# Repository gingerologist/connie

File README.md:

# Connie

Constance Emily Kent, the murder at Road Hill House.

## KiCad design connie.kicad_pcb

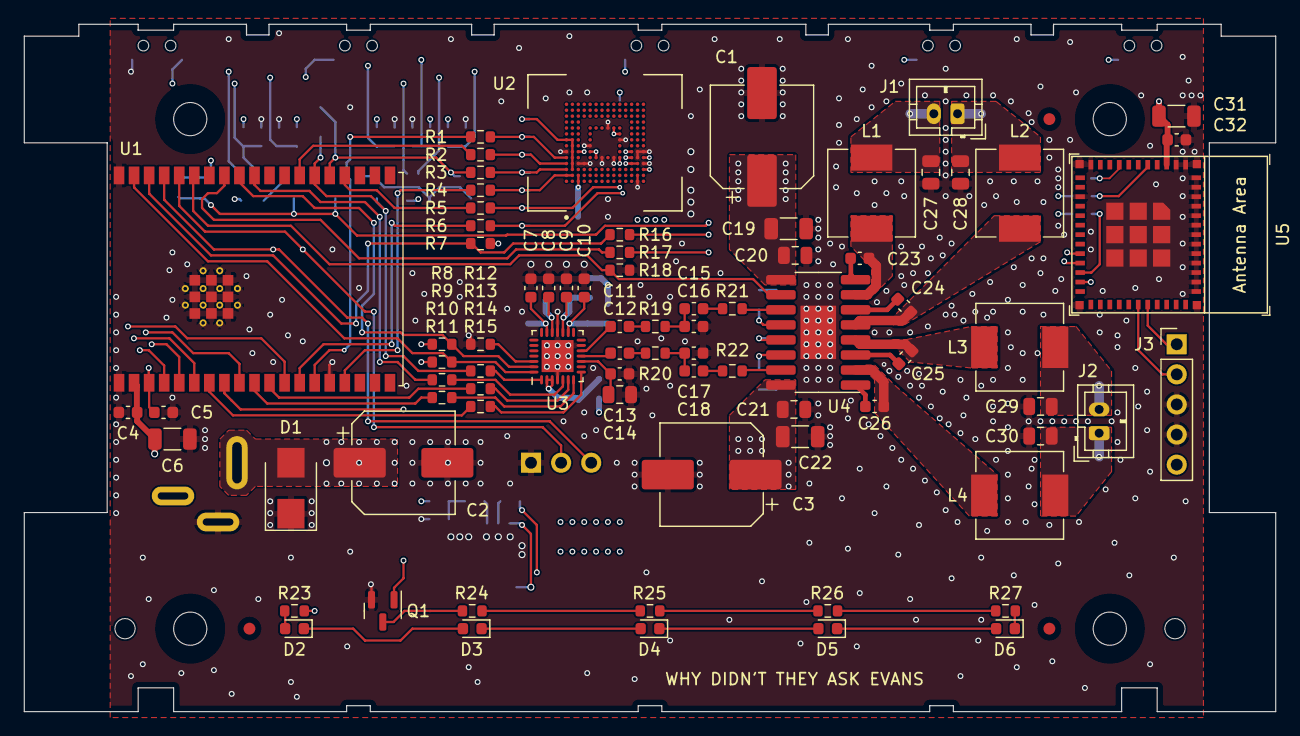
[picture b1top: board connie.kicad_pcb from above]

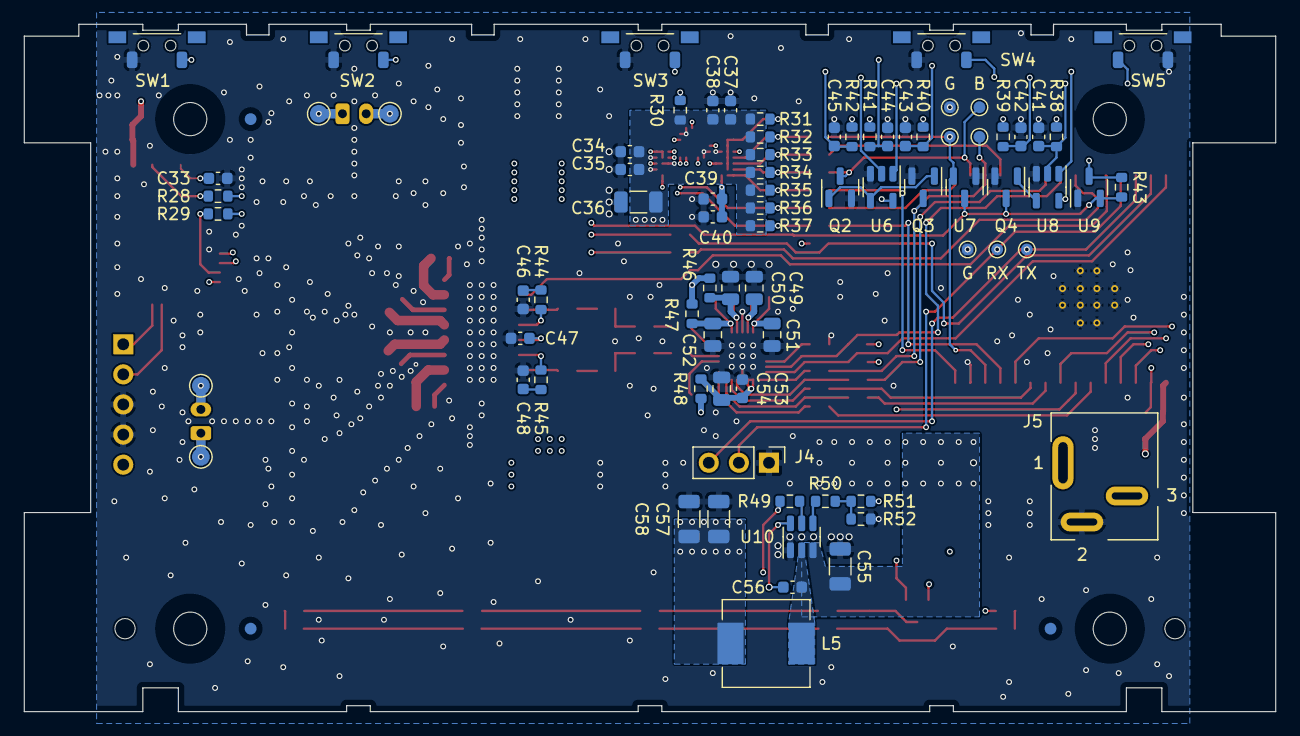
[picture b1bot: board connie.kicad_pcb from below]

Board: 4 copper layers, 105.6 x 58.0 mm, 168 parts (81 on the bottom side), 100 nets.

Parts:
C1, C2, C3: 220u,35V; CP_Elec_8x10.5
C4, C5, C7, C8, C9, C10, C13, C32, C33, C34, C37, C39, C41, C42, C43, C44, C45, C53: 0.1u; C_0603_1608Metric
C6, C19, C22, C31, C36, C55, C57, C58: 22u,1206,50V; C_1206_3216Metric
C11, C12, C15, C18, C35, C38, C40, C46, C48: 2.2u; C_0603_1608Metric
C14, C49, C50, C51, C52, C54: 10u,0805; C_0805_2012Metric
C16, C17: 47p; C_0603_1608Metric
C20, C21: 0.1u,0805,50V; C_0805_2012Metric
C23, C24, C25, C26, C47, C56: 1u,50V; C_0603_1608Metric
C27, C28, C29, C30: 0.47u,0805,50V; C_0805_2012Metric
D1: SMBJ15CA; D_SMB
D2, D3, D4, D5, D6: LED; LED_0603_1608Metric
FID1, FID2, FID3, FID4, FID5, FID6: Fiducial; Fiducial_1mm_Mask2mm
H1, H2, H3, H5: MountingHole; MountingHole_2.8mm_M2.5
H4, H6: MountingHole; MountingHole_1.7mm
J1, J2: Conn_01x02; JST_PH_B2B-PH-K_1x02_P2.00mm_Vertical
J3: Conn_01x05; PinHeader_1x05_P2.54mm_Vertical
J4: Conn_01x03; PinHeader_1x03_P2.54mm_Vertical
J5: Barrel_Jack_Switch; 69410X402002
L1, L2, L3, L4, L5: 10uH; Sunlord_MWSA0603_6.6x7.1_H3.0
Q1, Q2, Q3, Q4: DTC143Z; SOT-23
R1, R2, R3, R4, R5, R6, R10, R11, R12, R13, R14, R15, R16, R17: 33; R_0603_1608Metric
R7, R49: 100k; R_0603_1608Metric
R8, R9: 2.2k; R_0603_1608Metric
R18, R28, R29, R30, R31, R32, R33, R34, R35, R36, R37, R38, R39, R40, R41, R42, R43, R50: 10k; R_0603_1608Metric
R19, R20, R21, R22, R23, R24, R25, R26, R27, R44, R45: 100,1%; R_0603_1608Metric
R46, R47, R48: 0; R_0603_1608Metric
R51: 40.2k,1%; R_0603_1608Metric
R52: 13k,1%; R_0603_1608Metric
SW1, SW2, SW3, SW4, SW5: DIP_1188E
TP1, TP2, TP3, TP4, TP5, TP6, TP7: TestPoint; TestPoint_Pad_D1.0mm
TP10, TP11, TP12, TP13: TestPoint; TestPoint_Pad_D1.5mm
U1: ESP32-WROVER-E; ESP32-WROVER-E_Thermal_Vias
U2: EMMC(BGA153); EMMC_BGA153
U3: ES8388; QFN-28_EP_4x4_Pitch0.45mm
U4: CS8676E; CS8676E_SOP-16_3.9x9.9mm_P1.27mm
U5: ESP32-C3-MINI-1
U6, U8: 74LVC1G02; SOT-23-5
U7, U9: MAX803; SOT-23
U10: TPS562200; SOT-23-6

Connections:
+3V3: C4.1, C6.2, C31.2, C32.1, C34.2, C35.2, C36.2, C37.2, C38.2, C57.2, C58.2, L5.2, R7.1, R8.1, R9.1, R28.1, R29.1, R30.1, R31.1, R32.1, R33.1, R34.1, R35.1, R36.1, R37.1, R38.1, R39.2, R40.1, R41.1, R42.1, R43.1, R46.2, R47.2, R48.2, R51.1, U1.2 (3V3), U2.C6 (VCCQ), U2.E6 (VCC), U2.F5 (VCC), U2.J10 (VCC), U2.K9 (VCC), U2.M4 (VCCQ), U2.N4 (VCCQ), U2.P3 (VCCQ), U2.P5 (VCCQ), U5.3 (3V3), U6.5 (VCC), U8.5 (VCC), U9.3 (VCC)
+15V: C1.1, C2.1, C3.1, C19.2, C20.2, C21.2, C22.2, C55.2, D1.2 (A2), J5.1, R23.1, R49.2, U4.9 (PVCC), U4.16 (PVCC), U10.3 (VIN)
/C3_IO9: J3.5, U5.23 (IO9)
/C3_RXD0: J3.2, U5.30 (IO22)
/C3_RXD1: R16.2, U5.20 (IO6)
/C3_TXD0: J3.1, U5.31 (IO21)
/C3_TXD1: R17.2, U5.21 (IO7)
/CLK: R6.1, U1.13 (IO14)
/CMD: R5.1, U1.23 (IO15)
/D0: Q2.3 (C), R3.1, TP5.1, U1.24 (IO2)
/D1: R2.1, U1.26 (IO4)
/D2: R1.1, TP7.1, U1.14 (IO12), U7.2 (~RESET)
/D3: R4.1, U1.16 (IO13)
/DAT0: R3.2, R34.2, U2.A3 (DAT0)
/DAT1: R2.2, R33.2, U2.A4 (DAT1)
/DAT2: R1.2, R32.2, U2.A5 (DAT2)
/DAT3: R4.2, R35.2, U2.A2 (NC), U2.B2 (DAT3)
/DATN: R31.2, U2.A8 (NC), U2.B3 (DAT4), U2.B4 (DAT5), U2.B5 (DAT6), U2.B6 (DAT7), U2.B7 (NC), U2.B8 (NC)
/DIN: R14.1, U1.11 (IO26)
/DOUT: R15.1, U1.7 (IO35)
/EN: C5.2, C33.2, Q4.3 (C), R43.2, U1.3 (EN), U5.8 (EN), U7.3 (VCC), U9.2 (~RESET)
/LED: Q1.1 (B), U1.8 (IO32)
/LOUT1: C15.2, C16.2, R19.2
/LRCK: R11.1, U1.10 (IO25)
/MCLK: Q3.3 (C), R13.1, TP4.1, U1.25 (IO0)
/MODE: C41.2, R38.2, SW5.3, U1.5 (SENSOR_VN), U6.1, U8.2
/OUTNL: C24.1, L2.2, U4.5 (OUTNL)
/OUTNL2: C28.2, J1.1, L2.1, TP11.1
/OUTNR: C25.1, L3.2, U4.4 (OUTNR)
/OUTNR2: C29.1, J2.2, L3.1, TP13.1
/OUTPL: C23.1, L1.2, U4.7 (OUTPL)
/OUTPL2: C27.1, J1.2, L1.1, TP10.1
/OUTPR: C26.1, L4.2, U4.2 (OUTPR)
/OUTPR2: C30.2, J2.1, L4.1, TP12.1
/PA: R18.2, U1.33 (IO21), U4.10 (CTRL)
/PLAY: C42.1, R39.1, SW4.4, U1.9 (IO33), U6.2
/POWER: C45.1, R42.2, SW3.4, U1.4 (SENSOR_VP), U8.1
/PWRSW: C56.2, L5.1, U10.2 (SW)
/ROUT1: C17.1, C18.2, R20.2
/RXD0: J4.2, TP2.1, U1.34 (RXD0)
/RXD1: R17.1, U1.31 (IO19)
/SCL: R9.2, U1.37 (IO23), U3.28 (CCLK)
/SCLK: R10.1, U1.29 (IO5)
/SDA: R8.2, U1.30 (IO18), U3.27 (CDATA)
/TXD0: J4.3, TP1.1, U1.35 (TXD0)
/TXD1: R7.2, R16.1, U1.36 (IO22)
/VOL+: C44.1, R41.2, SW1.4, U1.12 (IO27)
/VOL-: C43.2, R40.2, SW2.4, U1.6 (IO34)
GND: C1.2, C2.2, C3.2, C4.2, C5.1, C6.1, C7.1, C8.1, C9.1, C10.1, C13.1, C14.1, C16.1, C17.2, C19.1, C20.1, C21.1, C22.1, C27.2, C28.1, C29.2, C30.1, C31.1, C32.2, C33.1, C34.1, C35.1, C36.1, C37.1, C38.1, C39.1, C40.1, C41.1, C42.2, C43.1, C44.2, C45.2, C46.2, C47.2, C48.2, C49.1, C50.1, C51.1, C52.1, C53.1, C54.1, C55.1, C57.1, C58.1, D1.1 (A1), J3.3, J3.4, J4.1, J5.2, Q1.2 (E), Q2.2 (E), Q3.2 (E), Q4.2 (E), R12.1, R18.1, R52.2, SW1.3, SW2.3, SW3.3, SW4.3, SW5.4, TP3.1, TP6.1, U1.1 (GND), U1.15 (GND), U1.38 (GND), U1.39 (GND), U2.A6 (VSS), U2.C4 (VSSQ), U2.D4 (NC), U2.E7 (VSS), U2.G5 (VSS), U2.H10 (VSS), U2.J5 (VSS), U2.K8 (VSS), U2.N1 (NC), U2.N2 (VSSQ), U2.N5 (VSSQ), U2.N6 (NC), U2.P4 (VSSQ), U2.P6 (VSSQ), U3.4 (DGND), U3.13 (HPGND), U3.18 (AGND), U3.29 (EP), U4.17 (PGND), U5.1 (GND), U5.2 (GND), U5.11 (GND), U5.14 (GND), U5.36 (GND), U6.3 (GND), U7.1 (GND), U8.3 (GND), U9.1 (GND), U10.1 (GND)
unnamed: C10.2, C52.2, R47.1, U3.16 (HPVDD)
unnamed: C11.1, U3.12 (LOUT1)
unnamed: C11.2, R19.1
unnamed: C12.1, U3.11 (ROUT1)
unnamed: C12.2, R20.1
unnamed: C13.2, C14.2, U3.10 (VREF)
unnamed: C15.1, R21.2
unnamed: C18.1, R22.2
unnamed: C23.2, U4.8 (BSPL)
unnamed: C24.2, U4.6 (BSNL)
unnamed: C25.2, U4.3 (BSNR)
unnamed: C26.2, U4.1 (BSPR)
unnamed: C39.2, C40.2, U2.C1 (NC), U2.C2 (VDDi)
unnamed: C46.1, R44.2
unnamed: C47.1, U4.13 (GVDD)
unnamed: C48.1, R45.2
unnamed: C8.2, C49.2, U3.19 (ADCVREF)
unnamed: C9.2, C50.2, R46.1, U3.17 (AVDD)
unnamed: C7.2, C51.2, U3.20 (VMID)
unnamed: C53.2, C54.2, R48.1, U3.2 (DVDD), U3.3 (PVDD)
unnamed: C56.1, U10.6 (VBST)
unnamed: D2.1 (K), D3.2 (A)
unnamed: D2.2 (A), R23.2
unnamed: D3.1 (K), D4.2 (A)
unnamed: D4.1 (K), D5.2 (A)
unnamed: D5.1 (K), D6.2 (A)
unnamed: D6.1 (K), R27.1
unnamed: Q1.3 (C), R24.2
unnamed: Q2.1 (B), Q3.1 (B), U6.4
unnamed: Q4.1 (B), U8.4
unnamed: R10.2, U3.5 (SCLK)
unnamed: R11.2, U3.7 (LRCK)
unnamed: R12.2, U3.26 (CE)
unnamed: R13.2, U3.1 (MCLK)
unnamed: R14.2, U3.6 (DSDIN)
unnamed: R15.2, U3.8 (ASDOUT)
unnamed: R21.1, U4.11 (INPL)
unnamed: R22.1, U4.15 (INPR)
unnamed: R24.1, R25.2
unnamed: R25.1, R26.2
unnamed: R26.1, R27.2
unnamed: R28.2, U5.5 (IO2)
unnamed: R29.2, U5.22 (IO8)
unnamed: R30.2, U2.K5 (RSTN)
unnamed: R5.2, R36.2, U2.M5 (CMD)
unnamed: R6.2, R37.2, U2.M6 (CLK)
unnamed: R44.1, U4.12 (INNL)
unnamed: R45.1, U4.14 (INNR)
unnamed: R49.1, U10.5 (EN)
unnamed: R50.1, U10.4 (VFB)
unnamed: R50.2, R51.2, R52.1

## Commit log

2022-03-18 add kicad file first
2022-03-18 add Library footprint
2022-03-18 add local footprint and symbol table
2022-03-18 add ignore
2022-03-19 add c3 module
2022-03-19 prepare to rename refs
2022-03-19 reannotate resistors
2022-03-19 reannotate caps
2022-03-21 prepare for manufacturing
2022-03-22 crude bom
